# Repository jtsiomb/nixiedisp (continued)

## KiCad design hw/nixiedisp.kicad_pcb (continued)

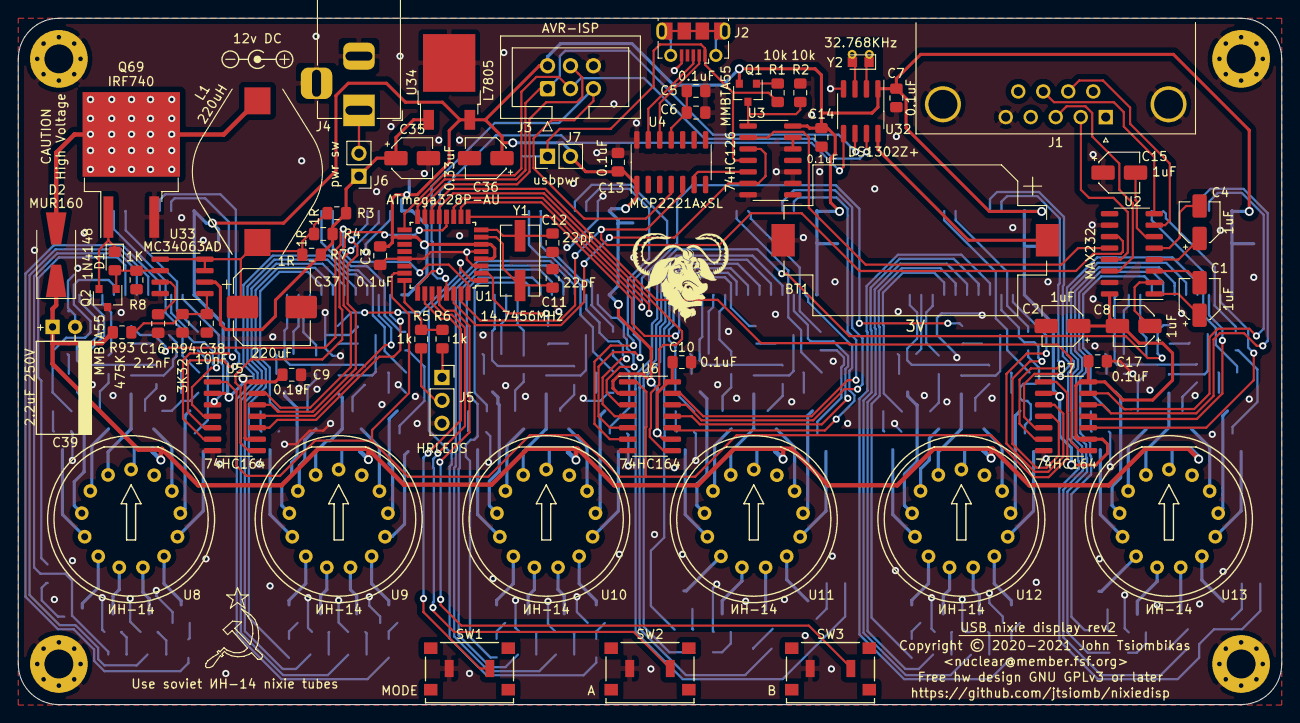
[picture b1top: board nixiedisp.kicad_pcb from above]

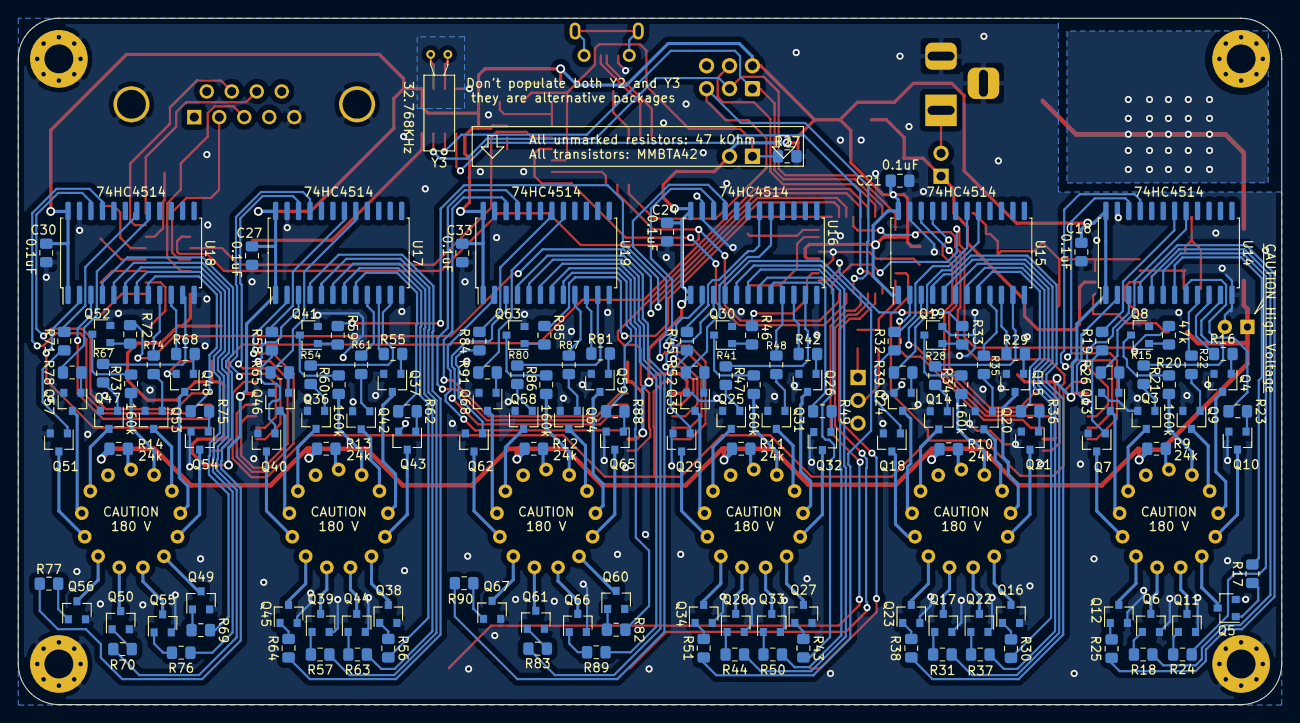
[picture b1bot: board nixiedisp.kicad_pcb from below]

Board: 2 copper layers, 140.0 x 76.1 mm, 229 parts (158 on the bottom side), 285 nets.

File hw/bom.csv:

Reference, Quantity,Description, Footprint,Mouser ID,Unit price,Cost
BT1 ,1,CR2032 battery holder,SMD battery holder Keystone 1060,534-1060TR,1.380 €,1.380 €
C3 C5 C6 C7 C9 C10 C13 C14 C17 C18 C21 C24 C27 C30 C33 ,15,0.1uF,SMD 0805,581-08055C104K,0.034 €,0.510 €
C11 C12 ,2,22pF,SMD 0805,80-C0805C220K1HACTU,0.032 €,0.064 €
C16 ,1,2.2nF,SMD 0805,187-CL21B222JBANNNC,0.020 €,0.020 €
C1 C2 C4 C8 C15 ,5,1uF electrolytic (RS232 option),SMD electrolytic 4x5.4,710-865060640001,0.136 €,0.680 €
C35 C36 ,2,0.33uF electrolytic,SMD electrolytic 4x5.4,710-865230640003,0.152 €,0.304 €
C37 ,1,220uF low-ESR electrolytic,SMD electrolytic 8x10,667-EEE-FP1V221AL,0.526 €,0.526 €
C38 ,1,10nF,SMD 0805,187-CL21B103JBANNNC,0.020 €,0.020 €
C39 ,1,2.2uF 250V,Through-hole radial,647-UVR2E2R2MED1TD,0.220 €,0.220 €
D1 ,1,1N4148,SMD SOD-323 (0805),750-1N4148WS-HF,0.106 €,0.106 €
D2 ,1,MUR160,SMD DO-214A (SMB),821-MUR160SR5G,0.250 €,0.250 €
J1 ,1,DB9 male (RS232 option),Through-hole DB9 male,523-L717SDE09P1ACH,1.350 €,1.350 €
J2 ,1,Micro-USB connector,USB Micro-B Molex-105017-0001,538-105017-0001,0.703 €,0.703 €
J3 ,1,AVR programming connector,2x3 male pin header 2.54mm pitch,710-61200621621,0.381 €,0.381 €
J4 ,1,DC barrel jack,barrel jack 2mm center pin,490-PJ-202A,0.500 €,0.500 €
J5 ,1,Hour-separator LED connector,1x3 female socket 2.54mm pitch,538-90147-1103,0.930 €,0.930 €
J6 ,1,pwr sw,1x2 male pin header 2.54mm pitch,538-22-28-4112,0.398 €,0.398 €
L1 ,1,220uH,SMD inductor 14x18.3,652-SDR1806-221KL,0.813 €,0.813 €
Q1 Q2 ,2,MMBTA55 PNP transistor,SMD SOT-23,863-MMBTA55LT1G,0.152 €,0.304 €
Q3-Q68 ,66,MMBTA42 NPN transistor,SMD SOT-23,863-MMBTA42LT1G,0.054 €,3.564 €
Q69 ,1,IRF740A,SMD TO-263-3,844-IRF740ASPBF,1.700 €,1.700 €
R1 R2 R27 ,4,10k,SMD 0805,71-CRCW080510K0JNEAC,0.033 €,0.132 €
R15-R20 R22-R26 R28-R33 R35-R39 R41-R46 R48-R52 R54-R59 R61-R65 R67-R72 R74-R78 R80-R85 R87-R91 ,66,47k,SMD 0805,652-CR0805FX-4702ELF,0.007 €,0.462 €
R21 R34 R47 R60 R73 R86 ,6,160k,SMD 0805,660-RK73H2ATTD1603F,0.013 €,0.078 €
R3 R4 R7 ,3,1 ohm,SMD 0805,603-RC0805FR-071RL,0.044 €,0.132 €
R5 R6 R8,2,1k,SMD 0805,71-CRCW08051K00JNEAC,0.033 €,0.066 €
R9 R10 R11 R12 R13 R14 ,6,24k,SMD 0805,660-RK73H2ATTD2402F,0.014 €,0.084 €
R93 ,1,475K,SMD 0805,667-ERJ-6ENF4753V,0.055 €,0.055 €
R94 ,1,3K32,SMD 0805,71-CRCW0805-3.32K-E3,0.048 €,0.048 €
SW1-SW3,1,Right-angle tactile button,SMD right-angle,113-TA34W2VTR,1.360 €,1.360 €
U1 ,1,Atmega328PB-AU,TQFP-32,556-ATMEGA328PB-AU,1.130 €,1.130 €
U14 U15 U16 U17 U18 U19 ,6,74HC4514,SOIC-24 wide,771-74HC4514D-T,0.864 €,5.184 €
U2 ,1,MAX232 (RS232 option),SOIC-16,595-MAX232DR,0.737 €,0.737 €
U3 ,1,74HC126,SOIC-14,595-SN74HC126DR,0.237 €,0.237 €
U32 ,1,DS1302Z+,SOIC-8,700-DS1302ZT&R,2.790 €,2.790 €
U33 ,1,MC34063AD,SOIC-8,595-MC34063ADR,0.296 €,0.296 €
U34 ,1,7805,SMD TO-252-2 DPAK,863-MC7805CDTRKG,0.356 €,0.356 €
U4 ,1,MCP2221AxSL,SOIC-14,579-MCP2221A-I/SL,1.680 €,1.680 €
U5 U6 U7 ,3,74HC164,SOIC-14,771-74HC164D-T,0.220 €,0.660 €
U8 U9 U10 U11 U12 U13 ,6,IN14,Nixie tube IN-14,,,0.000 €
Y1 ,1,14.7456MHz,SMD crystal ECS CSM3X 2pin 7.6x4.1mm,815-ABLS7M-14.745B2T,0.288 €,0.288 €
Y2 ,1,32.768KHz,SMD crystal 2-pin 2x1.2mm (alt.footprint Y3),815-ABS0632768KHZ61T,,0.000 €
Y3 ,1,32.768KHz,Through-hole crystal 3x8mm (alt.footprint Y2),695-CFS-20632768EZBB ,0.347 €,0.347 €
,2,Amber 3mm LED (hour sep.),Through-hole 3mm LED,859-LTL-1CHA,0.144 €,0.288 €
,,,,,,
,,,,,Total cost:,31.133 €

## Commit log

2020-12-26 PCB layout: nixie driver transistors and decoding pretty much final
2020-12-26 added RTC to the schematic
2020-12-27 PCB layout almost done
2020-12-27 finished the PCB rev1
2020-12-27 README
2020-12-27 schematic info
2020-12-30 minor pcb adjustments
2021-01-03 started on the firmware, added BOM
2021-01-08 firmware
2021-01-08 firmware debugging
2021-01-08 number mode works, added dot multiplexing to avoid fuzzy dots, and to reduce the brightness of the dots
2021-01-09 don't multiplex the digits with dots if no dots are visible
2021-01-09 updated BOM with components that need to changed for rev2, added power supply reference in the readme
2021-01-09 global brightness control, PWM and crossfading
2021-01-09 individually controlled cross-fade enable for each digit
2021-01-09 turn on hour sep. leds in clock mode, and keep the decimal point in the seconds tube
2021-01-10 expanded the readme and the help string in the firmware
2021-01-10 anti-cathode poisoning cycle once per day, and at startup
2021-01-10 clock leading zero option, and blanking command
2021-01-10 per-digit intensity control
2021-01-10 added option to display seconds in clock mode
2021-01-10 - now almost every command followed by a '?' queries the current option instead of setting it. - added option for when to run the anti-cathode poisoning cycling
2021-01-10 missing rtc_bcd conversion inline functions
2021-01-11 saving and restoring options from battery backed SRAM
2021-01-11 fixed date setting
2021-01-15 - fixed mistakes in the schematic - updated the PCB for the fixes - in process of adding a proper serial port with a max232
2021-01-15 halved the hour separator brightness levels to 64, to avoid flicker. It used to update at 40hz which was clearly visible. Now it should update at 80hz.
2021-01-15 forgot to change the help text to reflect the reduced hour separator brightness range
2021-01-16 implemented the timer mode
2021-01-16 changed the decimal point handling to allow showing any number of dots instead of necessarilly one. useful for showing dates, or arbitrarilly juggling moving dots...
2021-01-16 - added button handling in firmware (untested) - holding down button B while in clock mode shows the date - pressing buttons A/B while in number mode increments/decrements the number - pressing butto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
2021-01-16 dropped the interrupt because I was too lazy to hardware-debounce the buttons, now polling and counting stable states for debouncing
2021-01-16 added option for 12hr clock
2021-01-19 lots of changes, redesigning most of the PCB
2021-01-19 PCB rev2 layout in progress
2021-01-22 - fw: added check in the build system, to make sure we don't exceed the data space of the microcontroller - fw: added missing help item
2021-01-22 fw: accept spaces in numbers and treat them as blank digits
2021-02-09 rev2 board
2021-02-10 added support for atmega328pb
2021-02-10 moved the help string to program space
2021-02-10 now that the huge string is in program space, there's no need for the data overflow detection hack in the makefile
2021-02-11 started a config gui
2021-02-13 added simple commandline tool for displaying CPU usage
2021-02-14 hacking on the GUI program
2021-02-14 more GUI hacking
2021-02-14 almost done with the main functionality of the GUI
2021-02-14 more GUI code
2021-02-14 about dialog
2021-02-14 updated the readme
2021-02-15 - exported fresh gerbers - updated the readme
2021-02-15 added website to the readme
2021-02-15 readme fix
2021-02-15 updated the BOM
2021-02-15 added the BOM in csv format
2021-02-16 GUI fixes, and start of the windows port
2021-02-18 added clockset script
2021-02-18 - changed firmware to be less verbose when changing brightness, to reduce display flicker while dragging sliders in the GUI - nixiedisp-gui: added "reset defaults" menu action
2021-02-27 anti-cathode poisoning cycle script
2021-02-27 added install-scripts script
2022-04-03 port nixiedisp-gui to macos
2022-04-07 firmware update: add manual time/date setting
